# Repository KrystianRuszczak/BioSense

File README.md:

# BioSense

BioSense is an experimental biosignal acquisition platform built around an ESP32. The project includes firmware and a custom PCB design. It reads data from several sensors and can send it to a computer or an MQTT broker.

> **Disclaimer:** BioSense is an experimental project, not a medical device. It is not intended for diagnosis, patient monitoring, treatment decisions, or other medical use.

## Features

- ECG acquisition with an AD8232 module, lead-off detection, and heart-rate estimation
- GSR measurement
- MAX30102 heart-rate and SpO₂ estimation
- MLX90614 temperature measurement
- Battery voltage measurement and charge-level estimation

## Hardware

The firmware is configured for the classic ESP32. The KiCad schematics, PCB design: [`hardware/biosense_pcb/`](hardware/biosense_pcb/). See the [hardware README](hardware/biosense_pcb/README.md) for more information about the board and its main components.

The main GPIO assignments: [`main/include/biosense_config.hpp`](main/include/biosense_config.hpp):

## Requirements

- ESP-IDF and the components listed in [`main/idf_component.yml`](main/idf_component.yml)
- The ESP-IDF command-line tools, including `idf.py`
- An ESP32 board and sensors compatible with the project
- An MQTT broker with TLS enabled

## Configuration

Create a local secrets header from the example file.

**PowerShell:**

```powershell
New-Item -ItemType Directory -Force main/private
Copy-Item main/include/biosense_secrets.hpp.example main/private/biosense_secrets.hpp
```

**macOS or Linux:**

```sh
mkdir -p main/private
cp main/include/biosense_secrets.hpp.example main/private/biosense_secrets.hpp
```

Edit `main/private/biosense_secrets.hpp` with your Wi-Fi and service settings.

Set `UDP_TARGET_IP` to the address of the computer that will receive UDP packets. The example uses port `4210`.

For MQTT, configure the broker settings. `MQTT_BROKER_URI` must include a scheme and port, for example:

```text
mqtts://broker.example.com:8883
```

The TLS connection uses the ESP-IDF system certificate bundle.

## Build and flash

Open a terminal configured for ESP-IDF, then run:

```sh
idf.py set-target esp32
idf.py build
idf.py -p PORT flash monitor
```

Replace `PORT` with your board’s serial port, such as `COM3` on Windows or `/dev/ttyUSB0` on Linux. Run `set-target` when setting up the project for the first time or when changing the target chip.

ESP-IDF downloads the required managed components during project configuration or build.

## Data transmission with MQTT

Topics use the `biosense/<MQTT_DEVICE_ID>/` prefix.

| Topic | Contents |
| --- | --- |
| `metrics` | Current measurements and sensor states (JSON) |
| `ecg` | ECG sample batches (JSON) |
| `gsr` | GSR sample batches (JSON) |
| `events` | Button events (JSON) |
| `status` | Device online/offline status |

## Repository layout

```text
main/                   ESP-IDF firmware
  include/              Configuration and module interfaces
  net/                  Wi-Fi, UDP, and MQTT
  sensors/              Sensor acquisition and data conversion
  signal/               ECG signal processing
  io/                   Buttons, buzzer, and LEDs
  power/                Battery-level estimation
hardware/biosense_pcb/  KiCad schematics and PCB design
```

## Security and privacy

Do not commit Wi-Fi passwords, MQTT credentials, or private certificates. Store local credentials in `main/private/biosense_secrets.hpp`.

Biosignal measurements may be sensitive. Secure your broker, network, and data storage accordingly.

## License

The original BioSense firmware and software are licensed under the MIT License. See [LICENSE](LICENSE).

The hardware design files in `hardware/biosense_pcb/` are licensed under CERN-OHL-P-2.0. See the [hardware license](hardware/biosense_pcb/LICENSE).

Third-party software retains its respective license. The MAX3010x algorithms are covered by the license files in [`main/third_party/max3010x_algorithms/`](main/third_party/max3010x_algorithms/).

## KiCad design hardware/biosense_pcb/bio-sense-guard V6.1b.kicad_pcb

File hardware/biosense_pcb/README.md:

# BioSense PCB

## Main modules
- ESP32 / ESP32-S3
- AD8232 ECG
- GSR input
- MLX90614
- MAX30102
- battery measurement
- buzzer
- push buttons
- WS2812 LEDs

## Firmware pin mapping
See `main/include/biosense_config.hpp`.

## Fabrication
Production files for ordered revisions are stored in `fabrication/revX/`.

## License

Copyright (c) 2026 Krystian Ruszczak.

The hardware design files in this directory are licensed under CERN-OHL-P-2.0. See [LICENSE](LICENSE).

The design files are provided "as is", without warranty. The complete terms are in the license file.

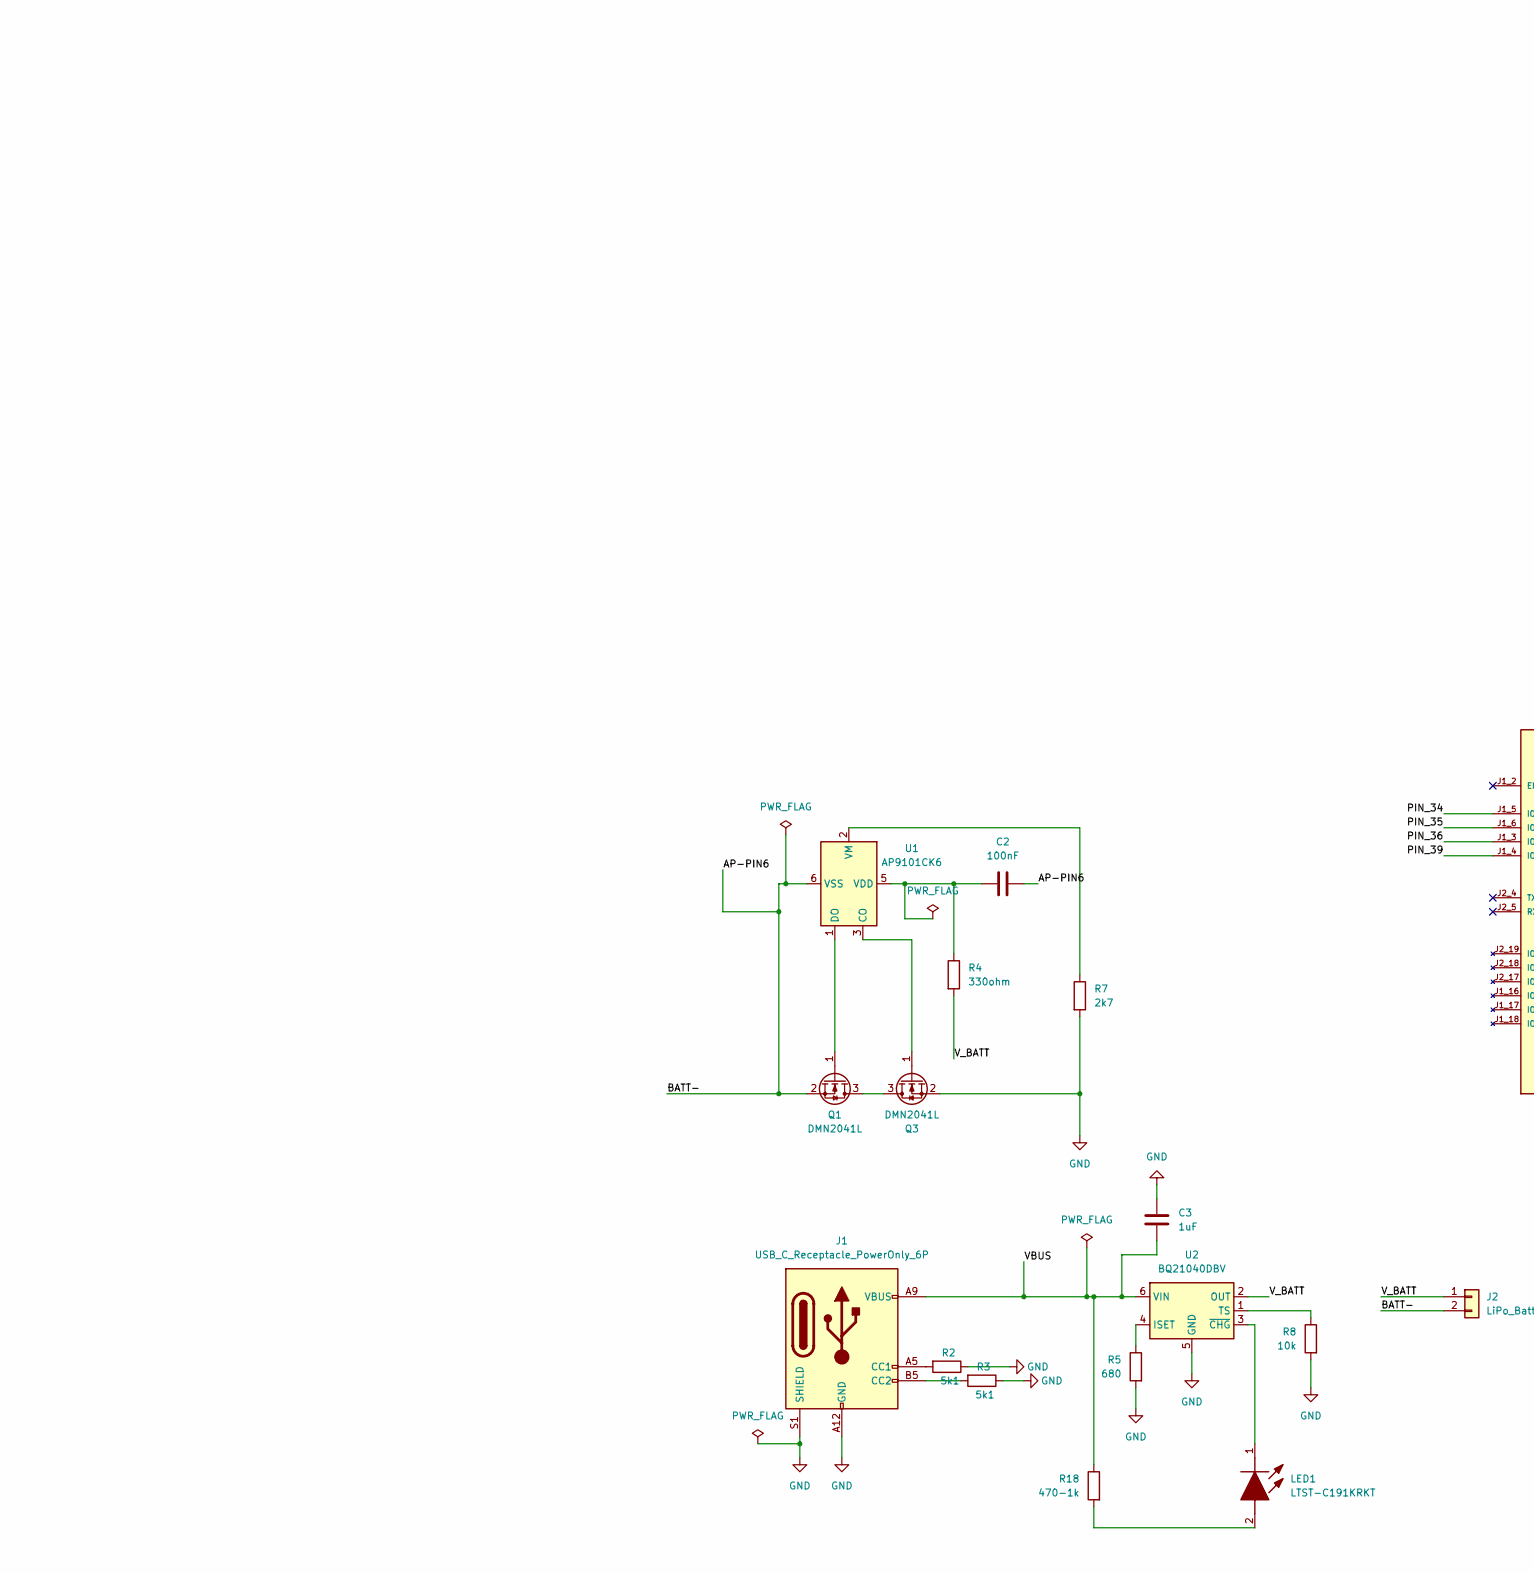
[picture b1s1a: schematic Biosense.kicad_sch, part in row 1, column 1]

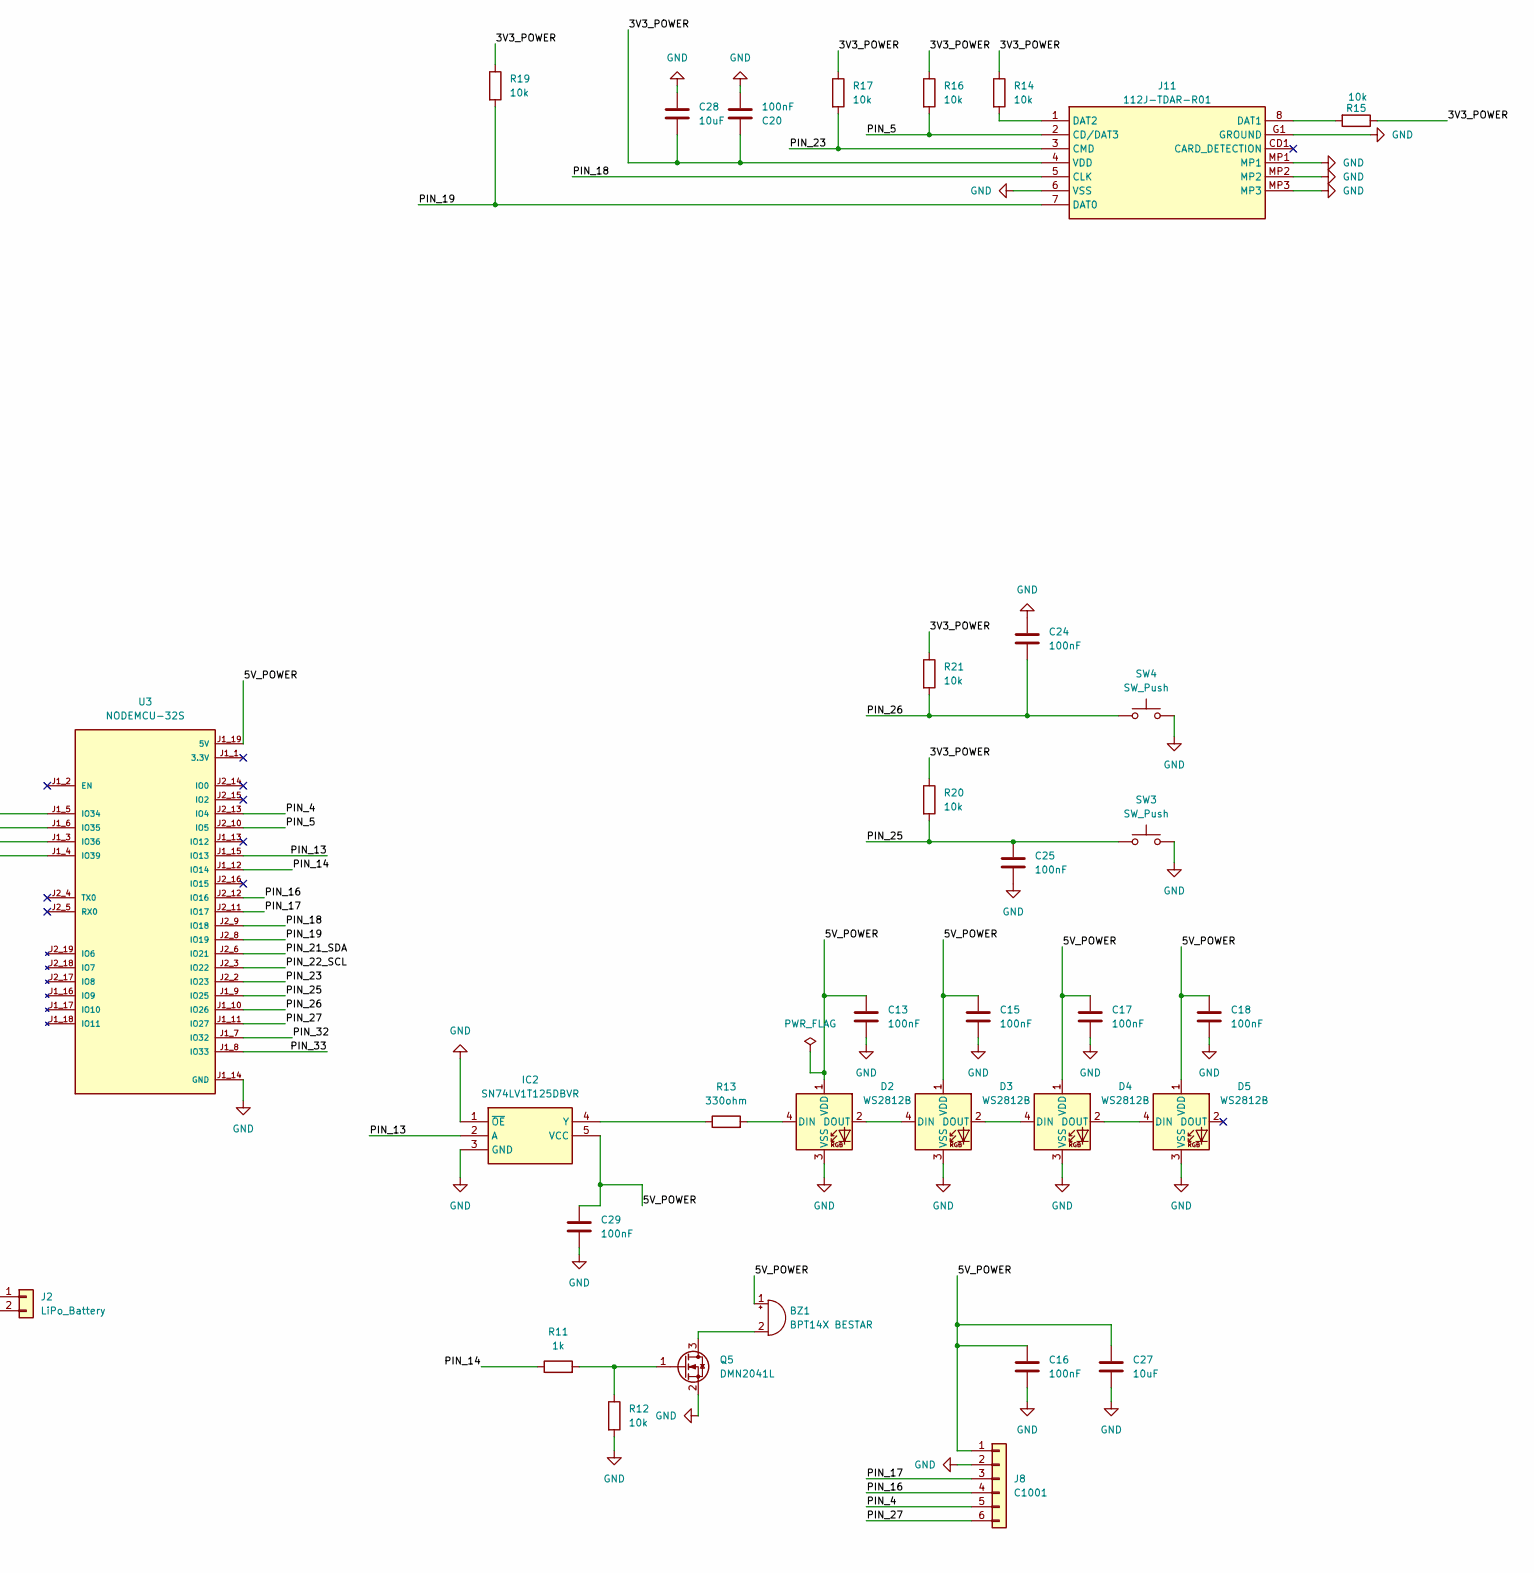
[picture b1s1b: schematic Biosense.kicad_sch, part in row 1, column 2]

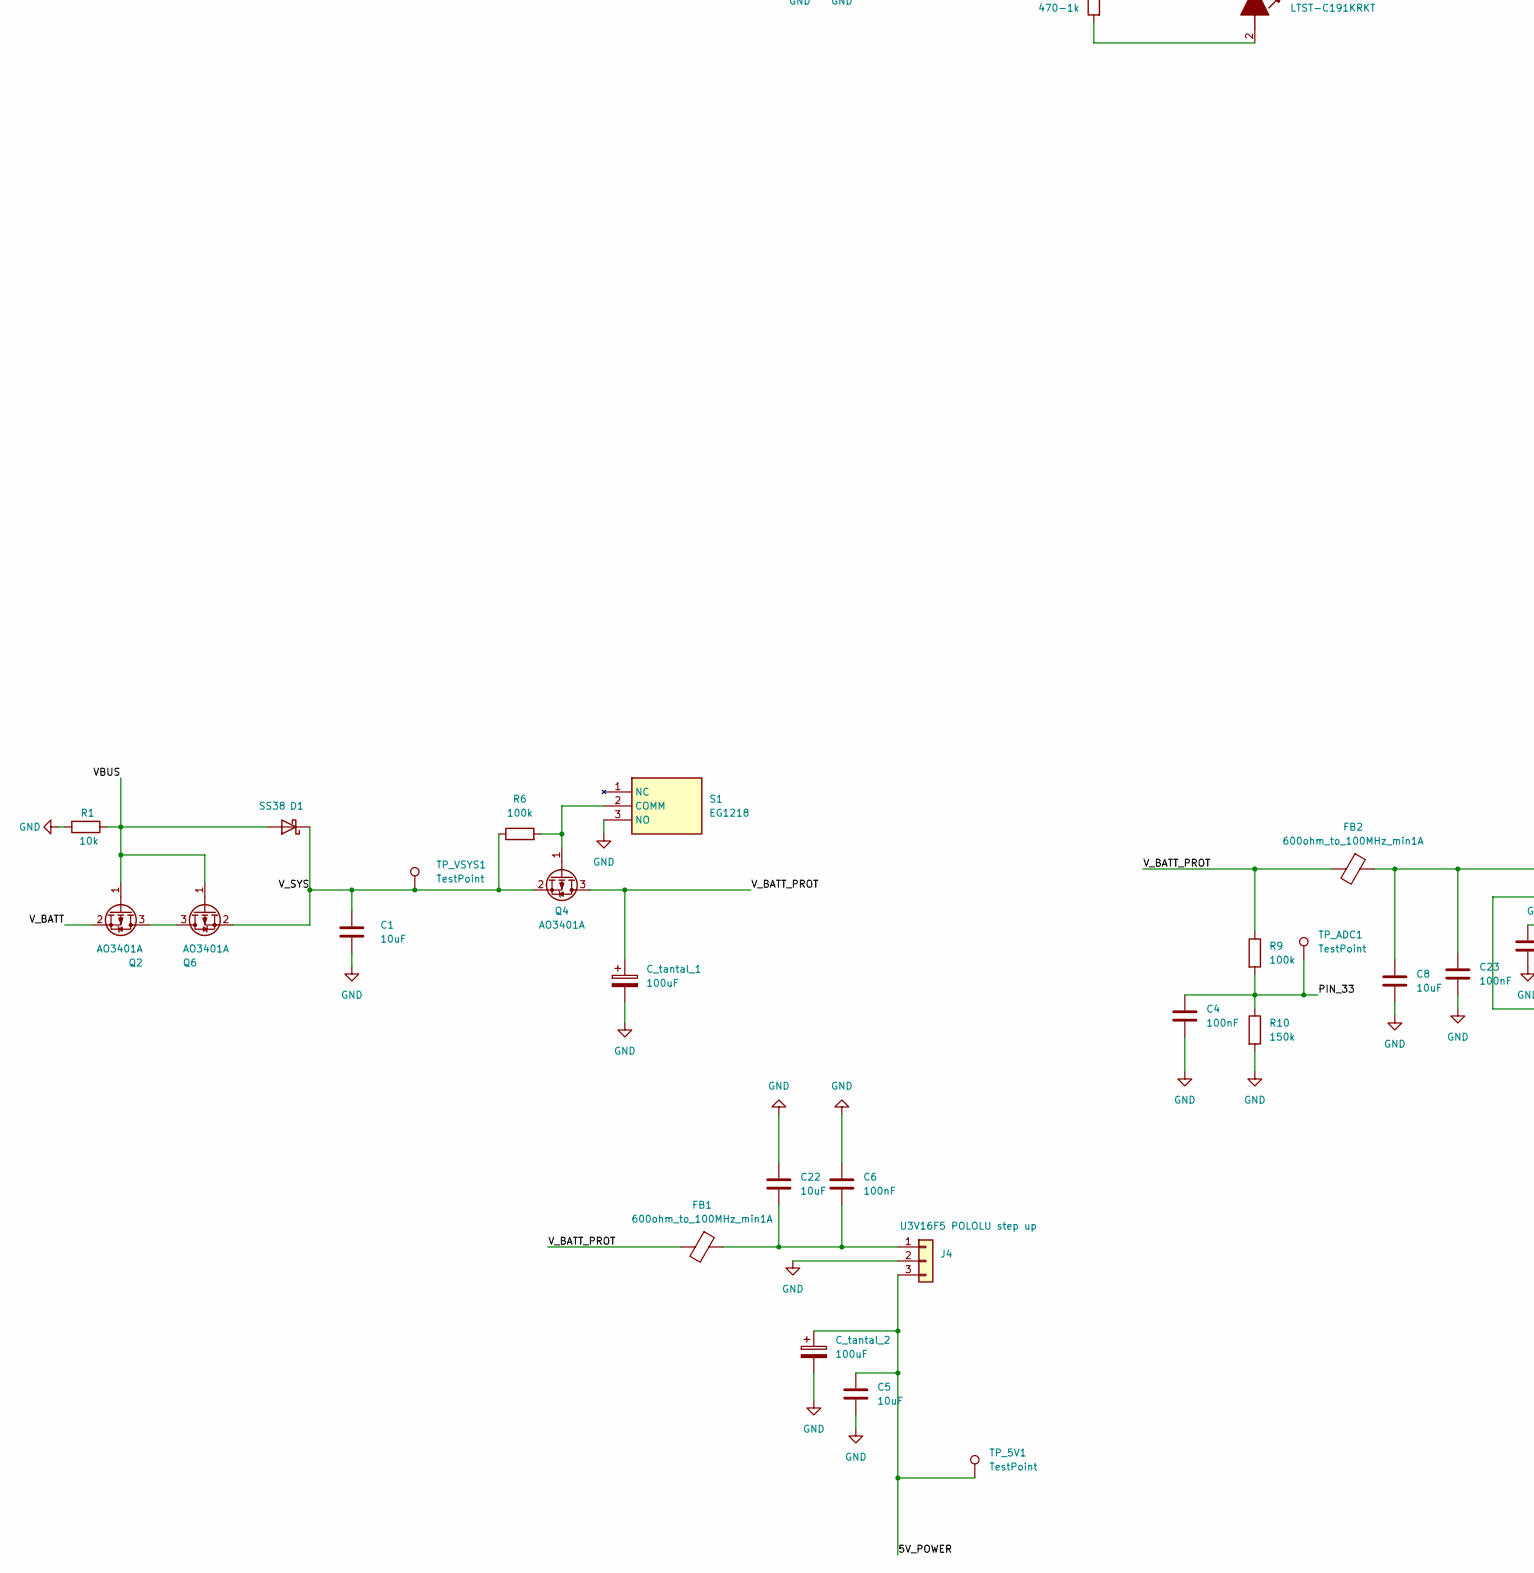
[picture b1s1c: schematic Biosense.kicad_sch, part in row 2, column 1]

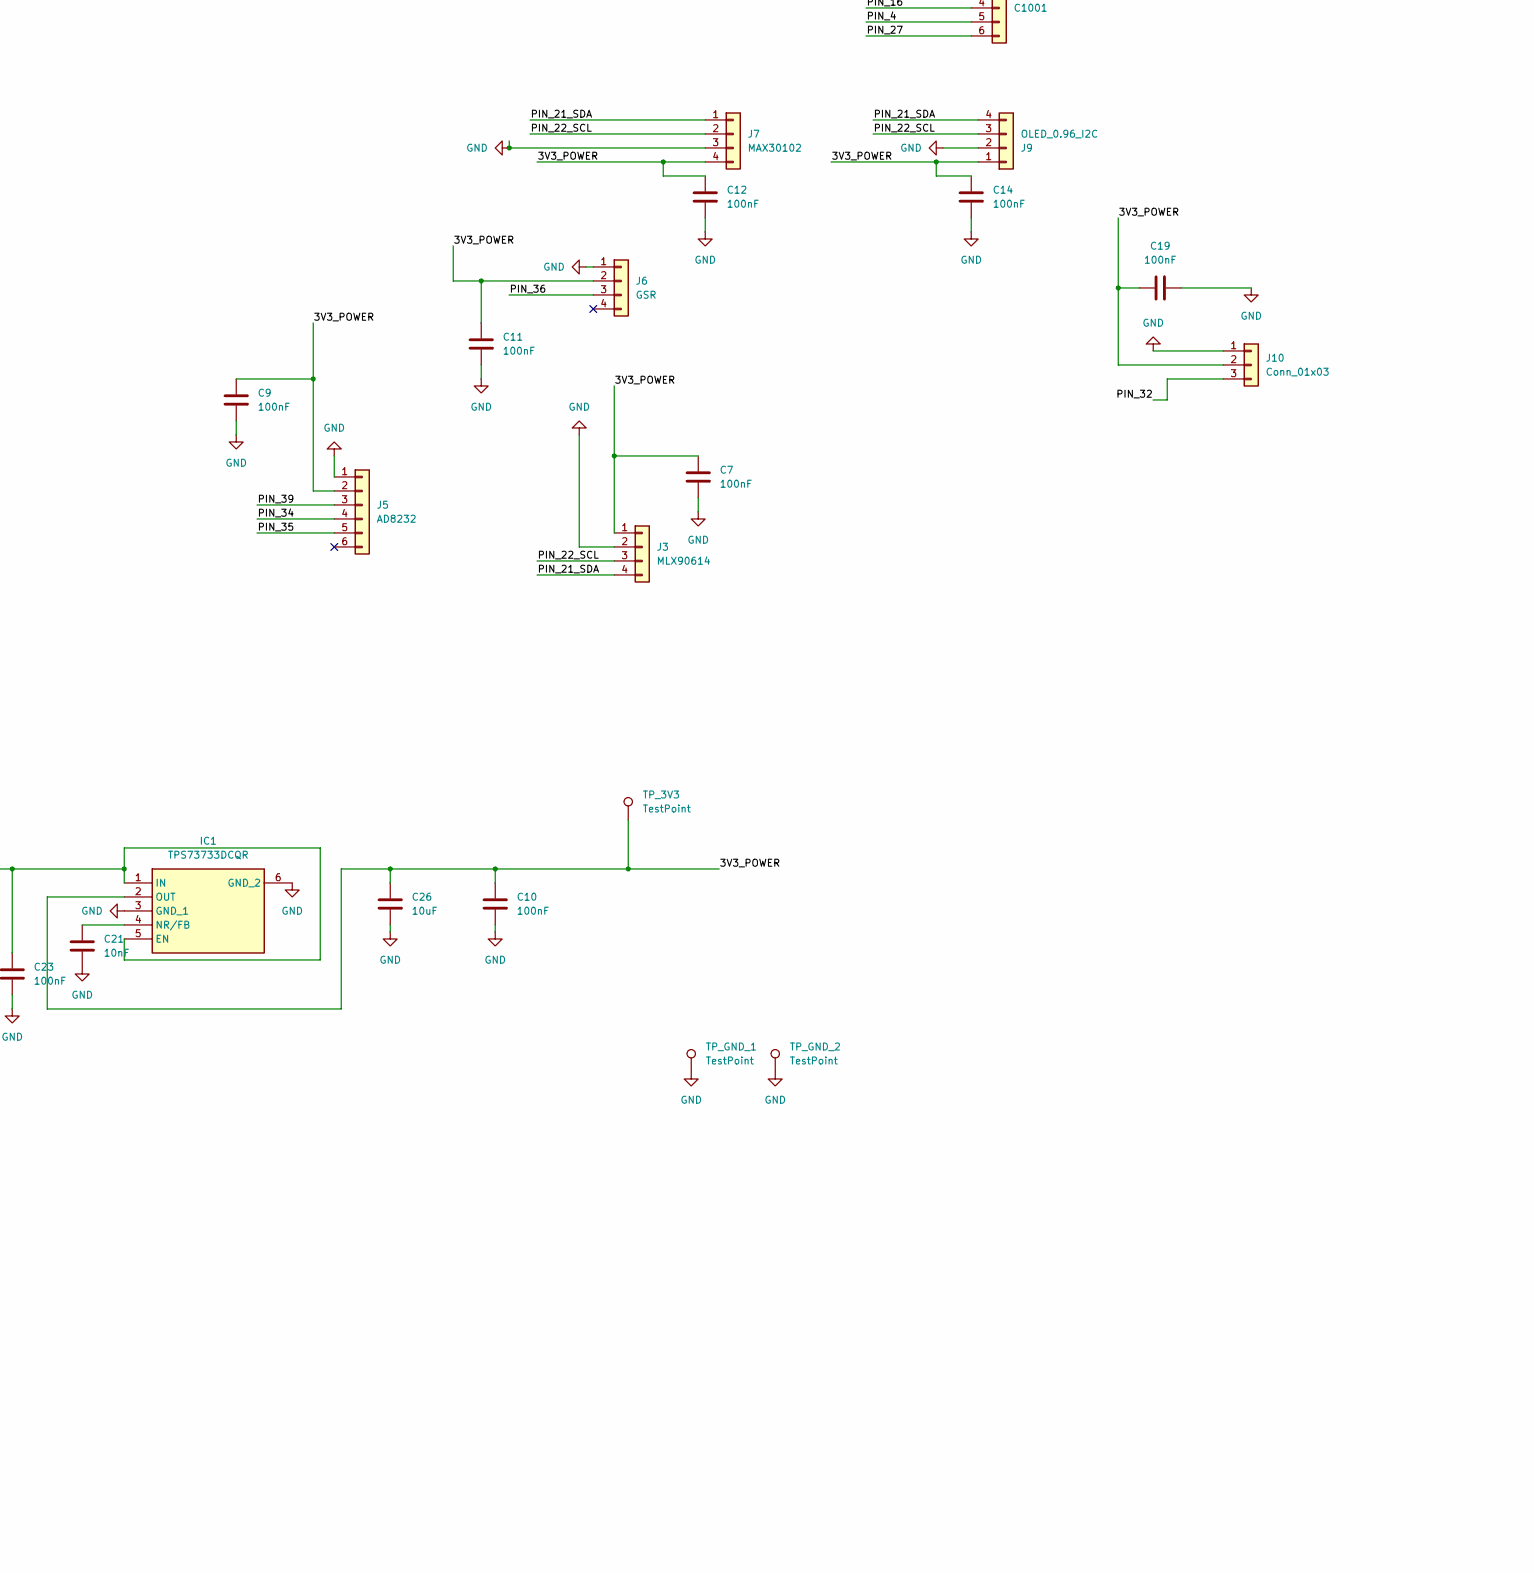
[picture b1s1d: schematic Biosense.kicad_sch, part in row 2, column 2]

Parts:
BZ1: BPT14X BESTAR; Buzzer_15x7.5RM7.6
C1, C5, C8, C22, C26, C27, C28: 10uF; C_0805_2012Metric_Pad1.18x1.45mm_HandSolder
C2, C4, C6, C7, C9, C10, C11, C12, C13, C14, C15, C16, C17, C18, C19, C20, C23, C24, C25, C29: 100nF; C_0805_2012Metric_Pad1.18x1.45mm_HandSolder
C3: 1uF; C_0805_2012Metric_Pad1.18x1.45mm_HandSolder
C21: 10nF; C_0805_2012Metric_Pad1.18x1.45mm_HandSolder
C_tantal_1, C_tantal_2: 100uF; CP_EIA-7343-31_Kemet-D_HandSolder
D1: SS38; D_SMA_Handsoldering
D2, D3, D4, D5: WS2812B; LED_WS2812B_PLCC4_5.0x5.0mm_P3.2mm
FB1, FB2: 600ohm_to_100MHz_min1A; R_0805_2012Metric_Pad1.20x1.40mm_HandSolder
IC1: TPS73733DCQR; SOT127P706X180-6N; Manufacturer_Part_Number TPS73733DCQR
IC2: SN74LV1T125DBVR; SOT-23-5_HandSoldering; Manufacturer_Part_Number SN74LV1T125DBVR
J1: USB_C_Receptacle_PowerOnly_6P; USB_C_Receptacle_GCT_USB4125-xx-x-0190_6P_TopMnt_Horizontal
J2: LiPo_Battery; JST_XH_B2B-XH-A_1x02_P2.50mm_Vertical
J3: MLX90614; PinHeader_1x04_P2.54mm_Vertical
J4: U3V16F5 POLOLU step up; PinSocket_1x03_P2.54mm_Vertical
J5: AD8232; PinHeader_1x06_P2.54mm_Vertical
J6: GSR; PinHeader_1x04_P2.54mm_Vertical
J7: MAX30102; PinHeader_1x04_P2.54mm_Vertical
J8: C1001; PinHeader_1x06_P2.54mm_Vertical
J9: OLED_0.96_I2C; PinHeader_1x04_P2.54mm_Vertical
J10: Conn_01x03; PinHeader_1x03_P2.54mm_Vertical
J11: 112J-TDAR-R01; 112JTDARR01; Manufacturer_Part_Number 112J-TDAR-R01
LED1: LTST-C191KRKT; LEDC1608X55N; Manufacturer_Part_Number LTST-C191KRKT
Q1, Q3, Q5: DMN2041L; SOT-23_Handsoldering
Q2, Q4, Q6: AO3401A; SOT-23_Handsoldering
R1, R8, R12, R14, R15, R16, R17, R19, R20, R21: 10k; R_0805_2012Metric_Pad1.20x1.40mm_HandSolder
R2, R3: 5k1; R_0805_2012Metric_Pad1.20x1.40mm_HandSolder
R4, R13: 330ohm; R_0805_2012Metric_Pad1.20x1.40mm_HandSolder
R5: 680; R_0805_2012Metric_Pad1.20x1.40mm_HandSolder
R6, R9: 100k; R_0805_2012Metric_Pad1.20x1.40mm_HandSolder
R7: 2k7; R_0805_2012Metric_Pad1.20x1.40mm_HandSolder
R10: 150k; R_0805_2012Metric_Pad1.20x1.40mm_HandSolder
R11: 1k; R_0805_2012Metric_Pad1.20x1.40mm_HandSolder
R18: 470-1k; R_0805_2012Metric_Pad1.20x1.40mm_HandSolder
S1: EG1218; Manufacturer_Part_Number EG1218
SW3, SW4: SW_Push; SW_PUSH_6mm
TP_3V3, TP_5V1: TestPoint; TestPoint_Pad_D1.5mm
TP_ADC1: TestPoint; TestPoint_Pad_D1.5mm
TP_GND_1, TP_GND_2: TestPoint; TestPoint_THTPad_D2.0mm_Drill1.0mm
TP_VSYS1: TestPoint; TestPoint_Pad_D1.5mm
U1: AP9101CK6; SOT-23-6_Handsoldering
U2: BQ21040DBV; SOT-23-6_Handsoldering
U3: NODEMCU-32S; MODULE_NODEMCU-32S; PARTREV V1

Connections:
/3V3_POWER: C7.1, C9.1, C10.1, C11.1, C12.1, C14.1, C19.2, C20.1, C26.1, C28.2, IC1.2 (OUT), J3.1, J5.2, J6.2, J7.4, J9.1, J10.2, J11.4 (VDD), R14.1, R15.1, R16.1, R17.1, R19.1, R20.1, R21.1, TP_3V3.1 (1_1)
/5V_POWER: BZ1.1 (+), C5.1, C13.1, C15.1, C16.1, C17.1, C18.1, C27.1, C29.1, C_tantal_2.1, D2.1 (VDD), D3.1 (VDD), D4.1 (VDD), D5.1 (VDD), IC2.5 (VCC), J4.3, J8.1, TP_5V1.1 (1_1), U3.J1_19 (5V)
/AP-PIN6: C2.2, J2.2, Q1.2 (S), U1.6 (VSS)
/PIN_4: J8.5, U3.J2_13 (IO4)
/PIN_5: J11.2 (CD/DAT3), R16.2, U3.J2_10 (IO5)
/PIN_13: IC2.2 (A), U3.J1_15 (IO13)
/PIN_14: R11.1, U3.J1_12 (IO14)
/PIN_16: J8.4, U3.J2_12 (IO16)
/PIN_17: J8.3, U3.J2_11 (IO17)
/PIN_18: J11.5 (CLK), U3.J2_9 (IO18)
/PIN_19: J11.7 (DAT0), R19.2, U3.J2_8 (IO19)
/PIN_21_SDA: J3.4, J7.1, J9.4, U3.J2_6 (IO21)
/PIN_22_SCL: J3.3, J7.2, J9.3, U3.J2_3 (IO22)
/PIN_23: J11.3 (CMD), R17.2, U3.J2_2 (IO23)
/PIN_25: C25.1, R20.2, SW3.1, U3.J1_9 (IO25)
/PIN_26: C24.2, R21.2, SW4.1, U3.J1_10 (IO26)
/PIN_27: J8.6, U3.J1_11 (IO27)
/PIN_32: J10.3, U3.J1_7 (IO32)
/PIN_33: C4.1, R9.2, R10.1, TP_ADC1.1 (1_1), U3.J1_8 (IO33)
/PIN_34: J5.4, U3.J1_5 (IO34)
/PIN_35: J5.5, U3.J1_6 (IO35)
/PIN_36: J6.3, U3.J1_3 (IO36)
/PIN_39: J5.3, U3.J1_4 (IO39)
/VBUS: C3.2, D1.2 (A), J1.A9 (VBUS), J1.B9 (VBUS), Q2.1 (G), Q6.1 (G), R1.1, R18.1, U2.6 (VIN)
/V_BATT: J2.1, Q2.2 (S), R4.2, U2.2 (OUT)
/V_BATT_PROT: C_tantal_1.1, FB1.2, FB2.2, Q4.3 (D), R9.1
/V_SYS: C1.1, D1.1 (K), Q4.2 (S), Q6.2 (S), R6.1, TP_VSYS1.1 (1_1)
GND: C1.2, C3.1, C4.2, C5.2, C6.1, C7.2, C8.2, C9.2, C10.2, C11.2, C12.2, C13.2, C14.2, C15.2, C16.2, C17.2, C18.2, C19.1, C20.2, C21.1, C22.1, C23.2, C24.1, C25.2, C26.2, C27.2, C28.1, C29.2, C_tantal_1.2, C_tantal_2.2, D2.3 (VSS), D3.3 (VSS), D4.3 (VSS), D5.3 (VSS), IC1.3 (GND_1), IC1.6 (GND_2), IC2.1 (~OE), IC2.3 (GND), J1.A12 (GND), J1.B12 (GND), J1.S1 (SHIELD), J3.2, J4.2, J5.1, J6.1, J7.3, J8.2, J9.2, J10.1, J11.6 (VSS), J11.G1 (GROUND), J11.MP1, J11.MP2, J11.MP3, Q3.2 (S), Q5.2 (S), R1.2, R2.1, R3.1, R5.2, R7.2, R8.2, R10.2, R12.2, S1.3 (NO), SW3.2, SW4.2, TP_GND_1.1 (1_1), TP_GND_2.1 (1_1), U2.5 (GND), U3.J1_14 (GND), U3.J2_1 (GND), U3.J2_7 (GND)
unnamed: BZ1.2 (-), Q5.3 (D)
unnamed: D2.4 (DIN), R13.2
unnamed: D2.2 (DOUT), D3.4 (DIN)
unnamed: D3.2 (DOUT), D4.4 (DIN)
unnamed: D4.2 (DOUT), D5.4 (DIN)
unnamed: C8.1, C23.1, FB2.1, IC1.1 (IN), IC1.5 (EN)
unnamed: C21.2, IC1.4 (NR/FB)
unnamed: IC2.4 (Y), R13.1
unnamed: J1.A5 (CC1), R2.2
unnamed: J1.B5 (CC2), R3.2
unnamed: C6.2, C22.2, FB1.1, J4.1
unnamed: J11.8 (DAT1), R15.2
unnamed: J11.1 (DAT2), R14.2
unnamed: LED1.2 (A), R18.2
unnamed: LED1.1 (K), U2.3 (~CHG)
unnamed: Q1.3 (D), Q3.3 (D)
unnamed: Q1.1 (G), U1.1 (DO)
unnamed: Q2.3 (D), Q6.3 (D)
unnamed: Q3.1 (G), U1.3 (CO)
unnamed: Q4.1 (G), R6.2, S1.2 (COMM)
unnamed: Q5.1 (G), R11.2, R12.1
unnamed: C2.1, R4.1, U1.5 (VDD)
unnamed: R7.1, U1.2 (VM)
unnamed: R5.1, U2.4 (ISET)
unnamed: R8.1, U2.1 (TS)

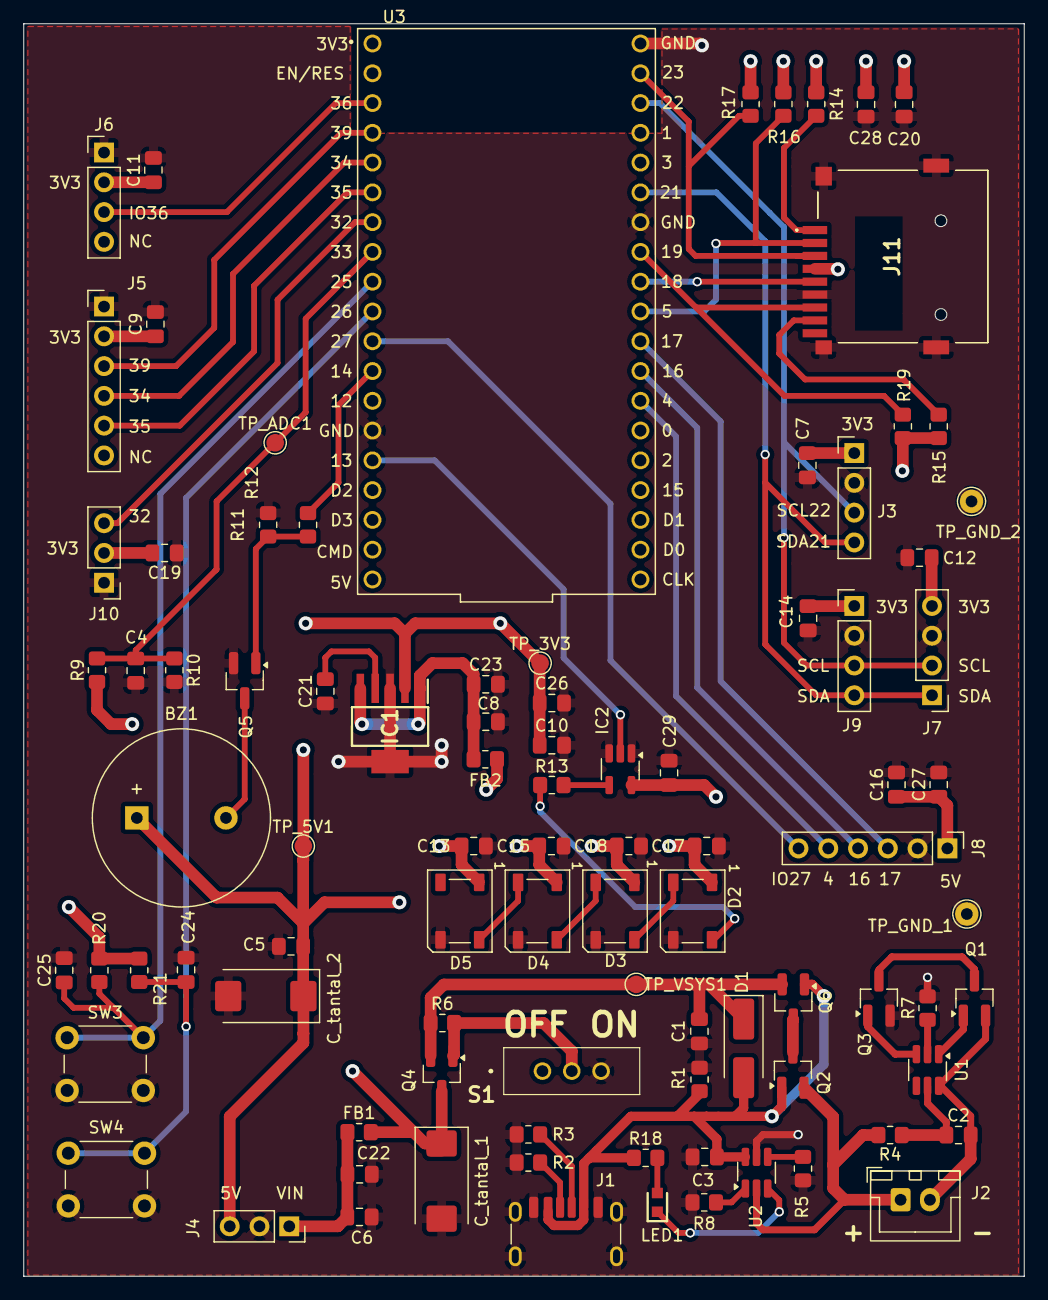
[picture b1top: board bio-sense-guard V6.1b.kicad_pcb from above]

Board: 4 copper layers, 85.3 x 106.8 mm, 92 parts (0 on the bottom side), 53 nets.
